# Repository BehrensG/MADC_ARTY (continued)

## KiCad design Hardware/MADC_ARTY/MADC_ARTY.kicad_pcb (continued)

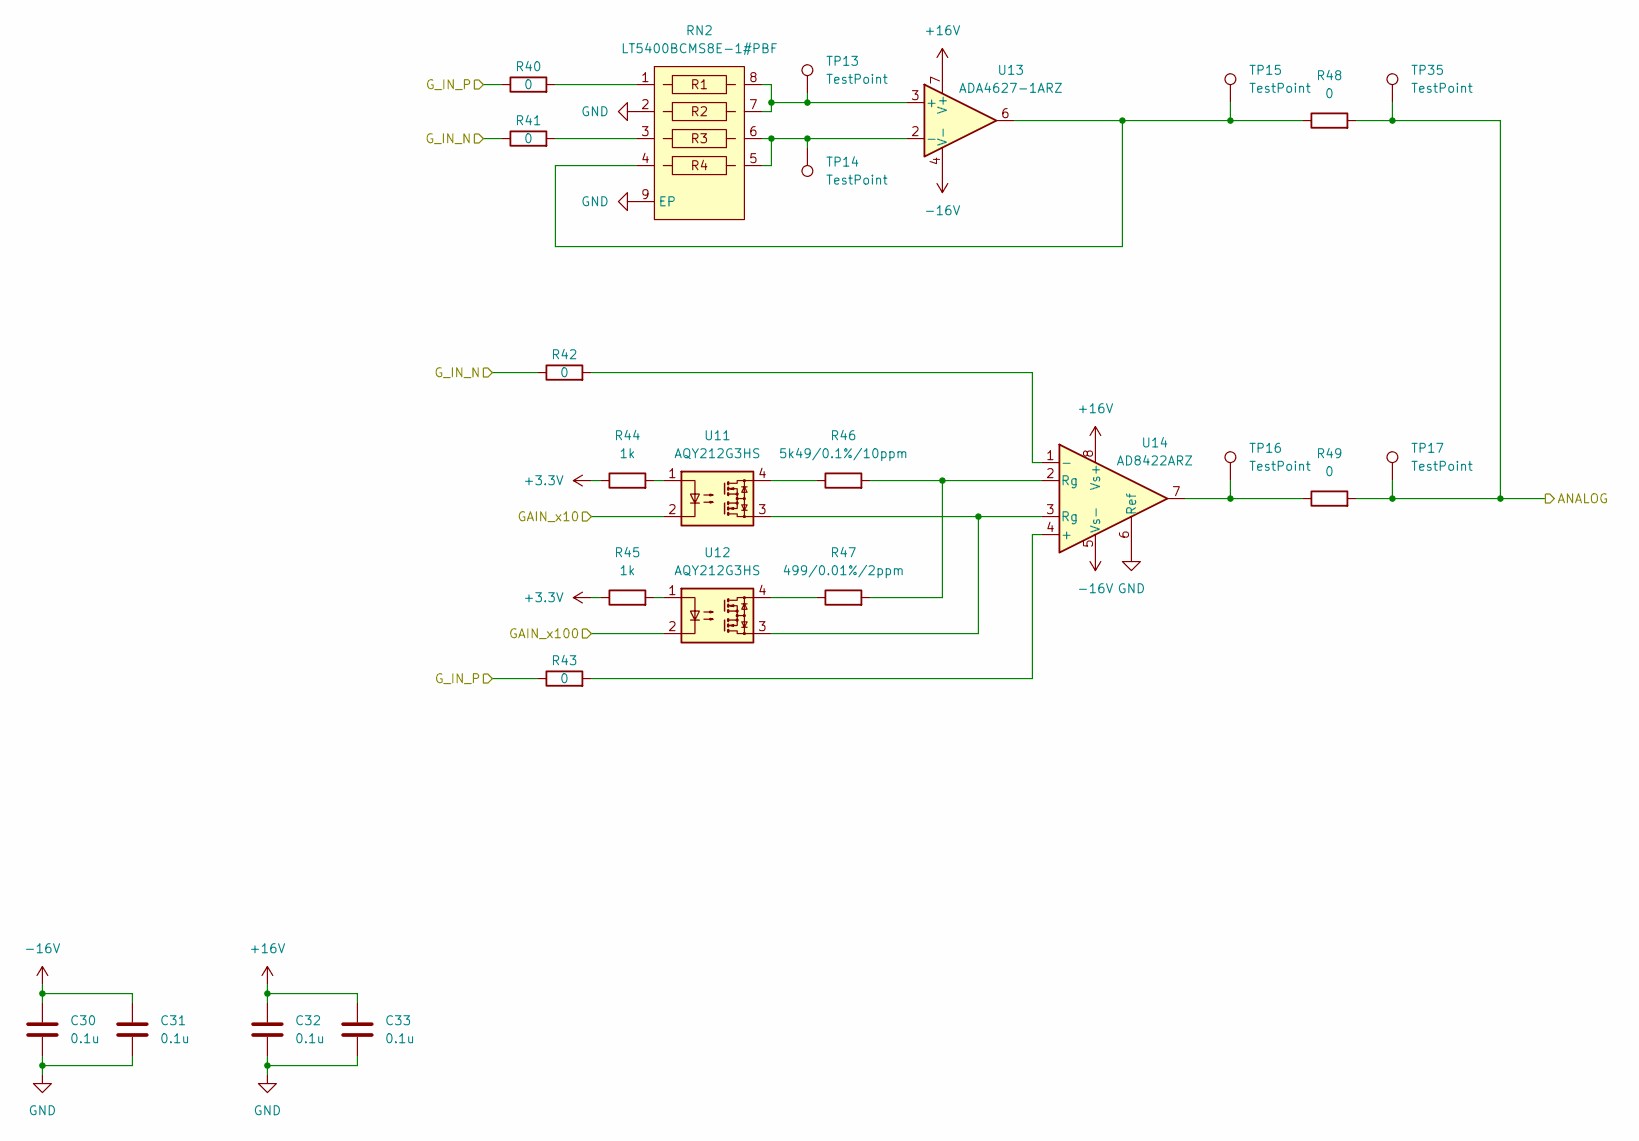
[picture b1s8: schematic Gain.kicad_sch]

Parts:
C30, C31, C32, C33: 0.1u; C_0603_1608Metric
R40, R41, R42, R43, R48, R49: 0; R_0603_1608Metric
R44, R45: 1k; R_0603_1608Metric
R46: 5k49/0.1%/10ppm; R_0603_1608Metric
R47: 499/0.01%/2ppm; R_0603_1608Metric
RN2: LT5400BCMS8E-1#PBF; MSOP-8-1EP_3x3mm_P0.65mm_EP1.73x1.85mm
TP13, TP14, TP15, TP16, TP17, TP35: TestPoint; TestPoint_Pad_D2.0mm
U11, U12: AQY212G3HS; SO-4_4.4x4.3mm_P2.54mm
U13: ADA4627-1ARZ; SOIC-8_3.9x4.9mm_P1.27mm
U14: AD8422ARZ; SOIC-8_3.9x4.9mm_P1.27mm

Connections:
+3.3V: R44.1, R45.1; also elsewhere on the board
+16V: C32.1, C33.1, U13.7 (V+), U14.8 (Vs+); also elsewhere on the board
-16V: C30.1, C31.1, U13.4 (V-), U14.5 (Vs-); also elsewhere on the board
/Block Diagram/ADC/AD_IN: R48.2, R49.2, TP17.1, TP35.1; also elsewhere on the board
/Block Diagram/Analog Channels1/OUT: R41.1, R42.1; also elsewhere on the board
/Block Diagram/Analog Channels/OUT: R40.1, R43.1; also elsewhere on the board
/Block Diagram/Gain/GAIN_x10: U11.2; also elsewhere on the board
/Block Diagram/Gain/GAIN_x100: U12.2; also elsewhere on the board
GND: C30.2, C31.2, C32.2, C33.2, RN2.2, RN2.9 (EP), U14.6 (Ref); also elsewhere on the board
unnamed: R40.2, RN2.1
unnamed: R41.2, RN2.3
unnamed: R44.2, U11.1
unnamed: R45.2, U12.1
unnamed: R46.1, U11.4
unnamed: R46.2, R47.2, U14.2 (Rg)
unnamed: R47.1, U12.4
unnamed: R48.1, RN2.4, TP15.1, U13.6
unnamed: R49.1, TP16.1, U14.7
unnamed: U11.3, U12.3, U14.3 (Rg)
unnamed: RN2.7, RN2.8, TP13.1, U13.3 (+)
unnamed: RN2.5, RN2.6, TP14.1, U13.2 (-)
unnamed: R43.2, U14.4 (+)
unnamed: R42.2, U14.1 (-)

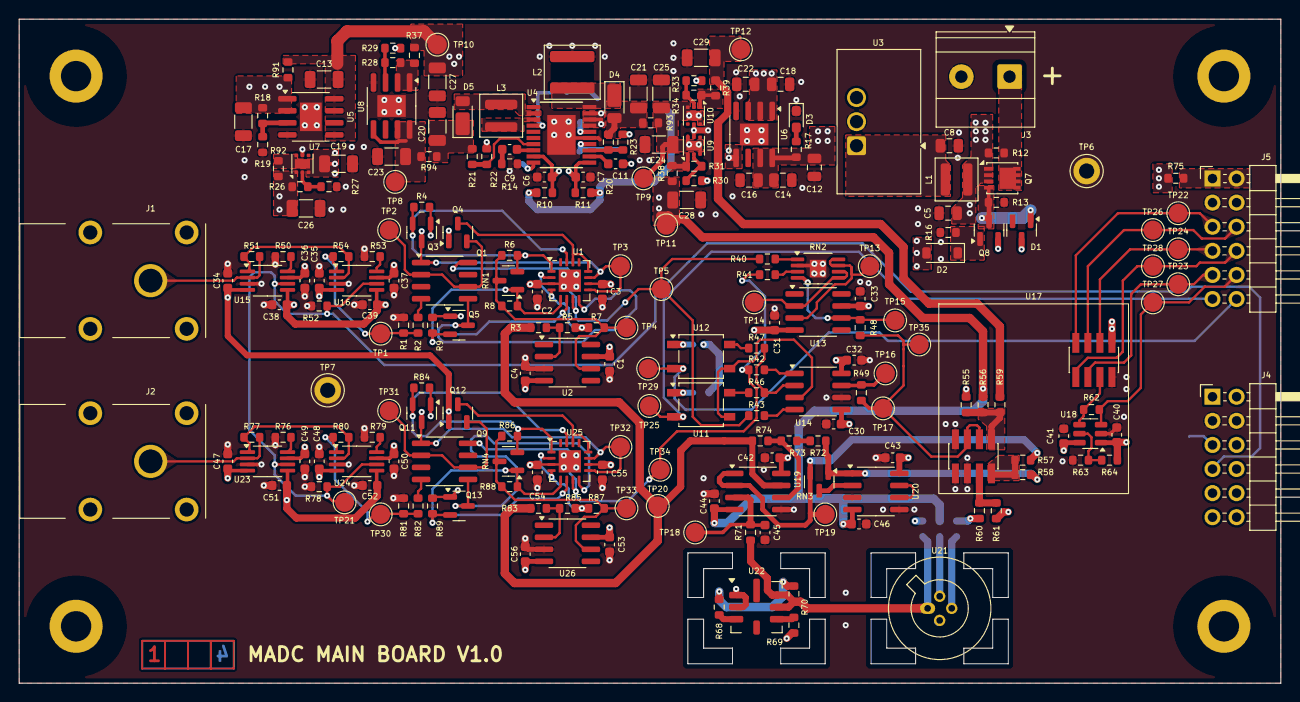
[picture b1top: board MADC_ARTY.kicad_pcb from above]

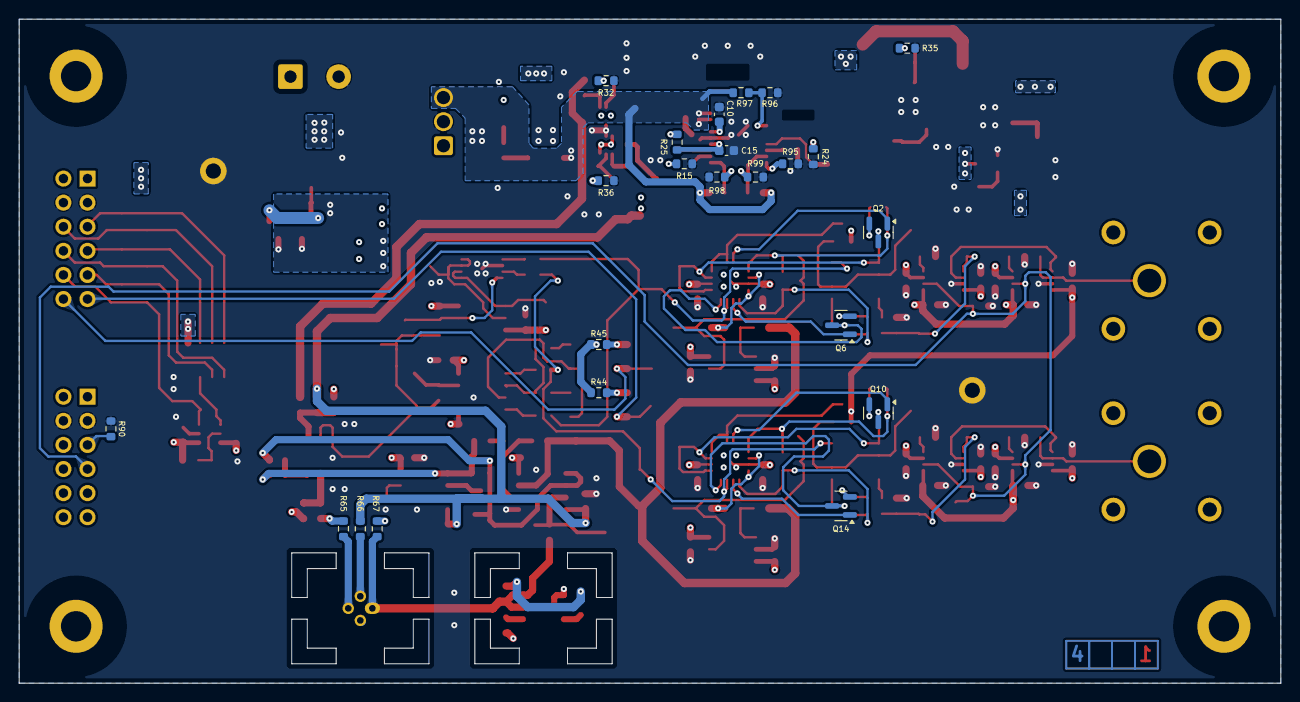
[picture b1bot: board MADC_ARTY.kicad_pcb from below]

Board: 4 copper layers, 133.0 x 70.0 mm, 251 parts (23 on the bottom side), 130 nets.

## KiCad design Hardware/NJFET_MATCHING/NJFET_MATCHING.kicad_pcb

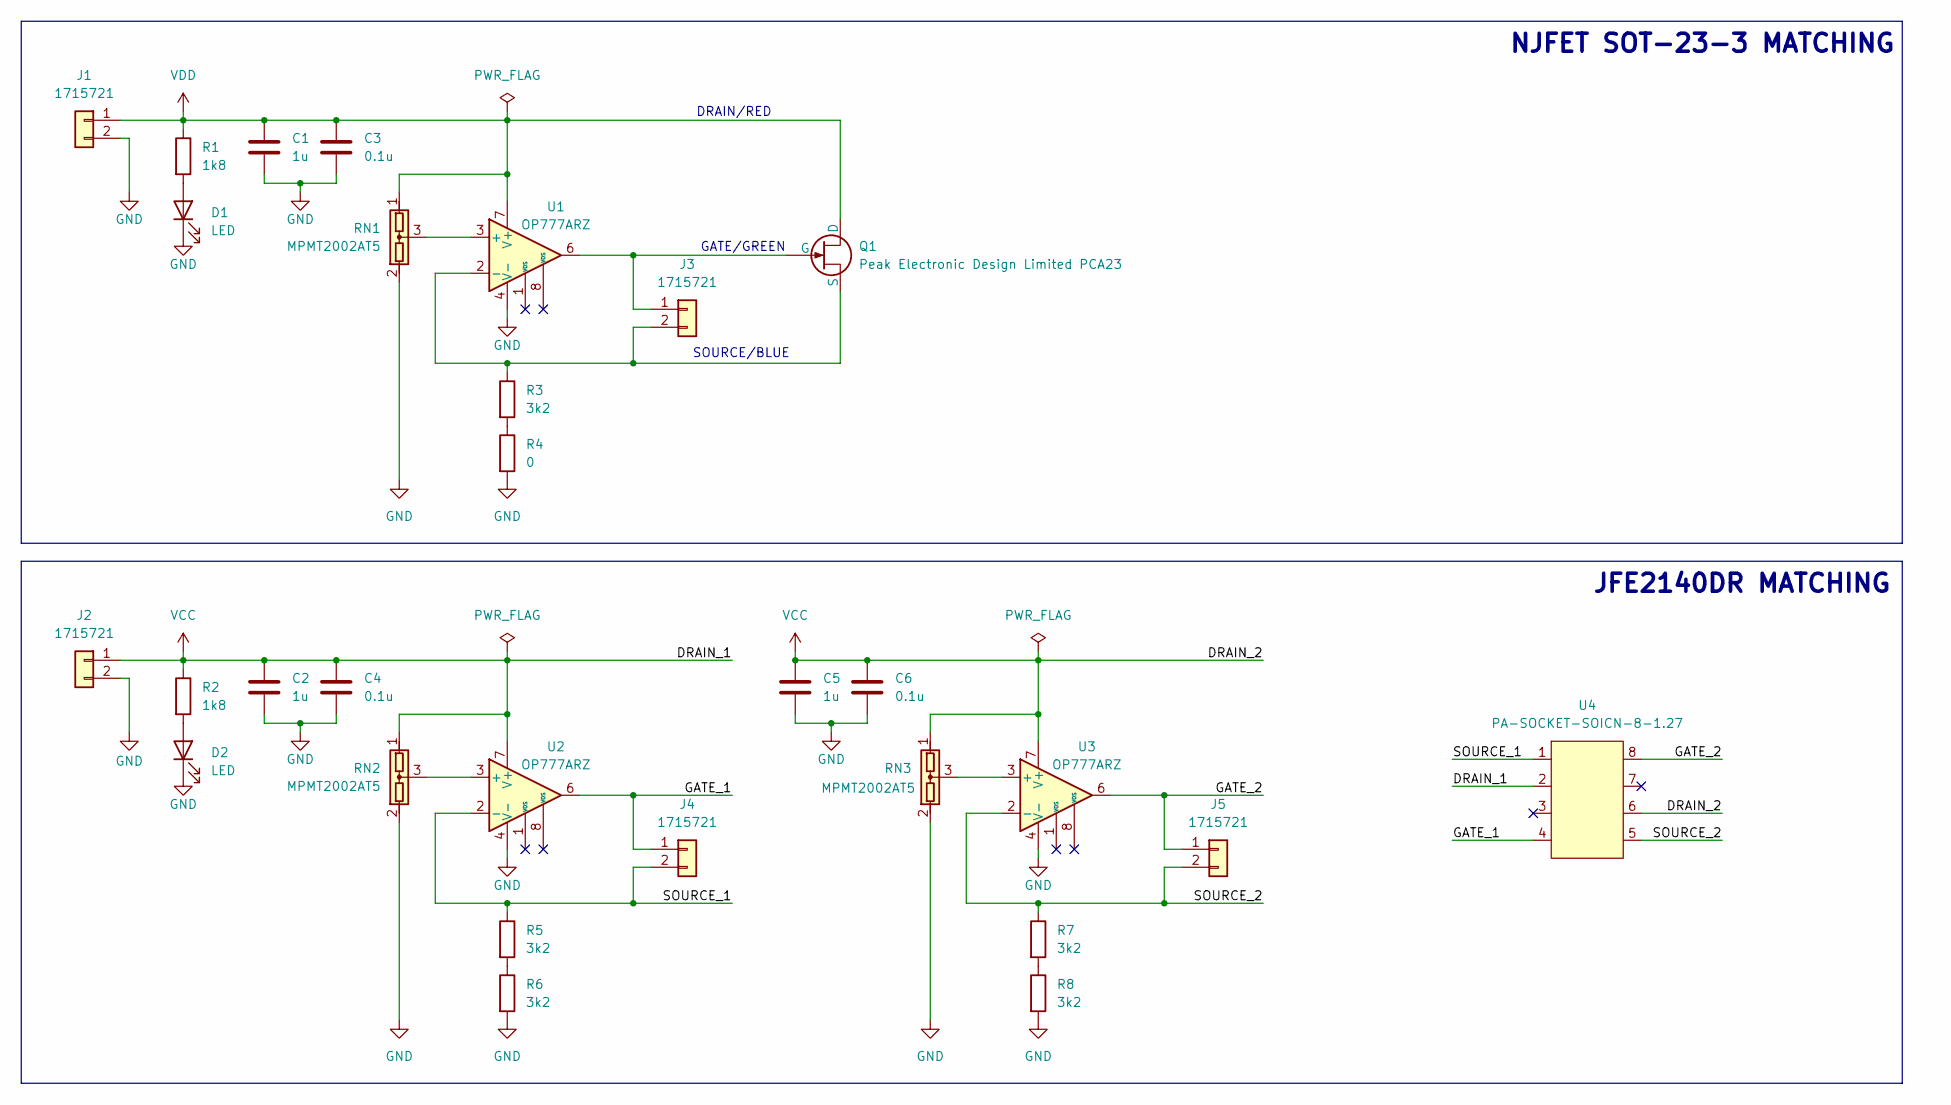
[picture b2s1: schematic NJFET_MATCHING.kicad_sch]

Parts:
C1, C2, C5: 1u; C_0603_1608Metric
C3, C4, C6: 0.1u; C_0603_1608Metric
D1, D2: LED; LED_0603_1608Metric
J1, J2, J3, J4, J5: 1715721; TerminalBlock_Phoenix_MKDS-1,5-2-5.08_1x02_P5.08mm_Horizont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
Q1: Peak Electronic Design Limited PCA23; PCA23
R1, R2: 1k8; R_0603_1608Metric
R3, R5, R6, R7, R8: 3k2; R_0603_1608Metric
R4: 0; R_0603_1608Metric
RN1, RN2, RN3: MPMT2002AT5; SOT-23
U1, U2, U3: OP777ARZ; SOIC-8_3.9x4.9mm_P1.27mm
U4: PA-SOCKET-SOICN-8-1.27; PA-SOCKET-SOICN-8-1_27

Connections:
/GATE_1: J4.1, U2.6, U4.4
/GATE_2: J5.1, U3.6, U4.8
/SOURCE_1: J4.2, R5.1, U2.2 (-), U4.1
/SOURCE_2: J5.2, R7.1, U3.2 (-), U4.5
GND: C1.2, C2.2, C3.2, C4.2, C5.2, C6.2, D1.1 (K), D2.1 (K), J1.2, J2.2, R4.2, R6.2, R8.2, RN1.2, RN2.2, RN3.2, U1.4 (V-), U2.4 (V-), U3.4 (V-)
unnamed: D1.2 (A), R1.2
unnamed: D2.2 (A), R2.2
unnamed: J3.1, Q1.2 (G), U1.6
unnamed: J3.2, Q1.3 (S), R3.1, U1.2 (-)
unnamed: R3.2, R4.1
unnamed: R5.2, R6.1
unnamed: R7.2, R8.1
unnamed: RN1.3, U1.3 (+)
unnamed: RN2.3, U2.3 (+)
unnamed: RN3.3, U3.3 (+)
VCC: C2.1, C4.1, C5.1, C6.1, J2.1, R2.1, RN2.1, RN3.1, U2.7 (V+), U3.7 (V+), U4.2, U4.6
VDD: C1.1, C3.1, J1.1, Q1.1 (D), R1.1, RN1.1, U1.7 (V+)

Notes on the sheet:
JFE2140DR MATCHING
NJFET SOT-23-3 MATCHING
SOURCE/BLUE
GATE/GREEN
DRAIN/RED

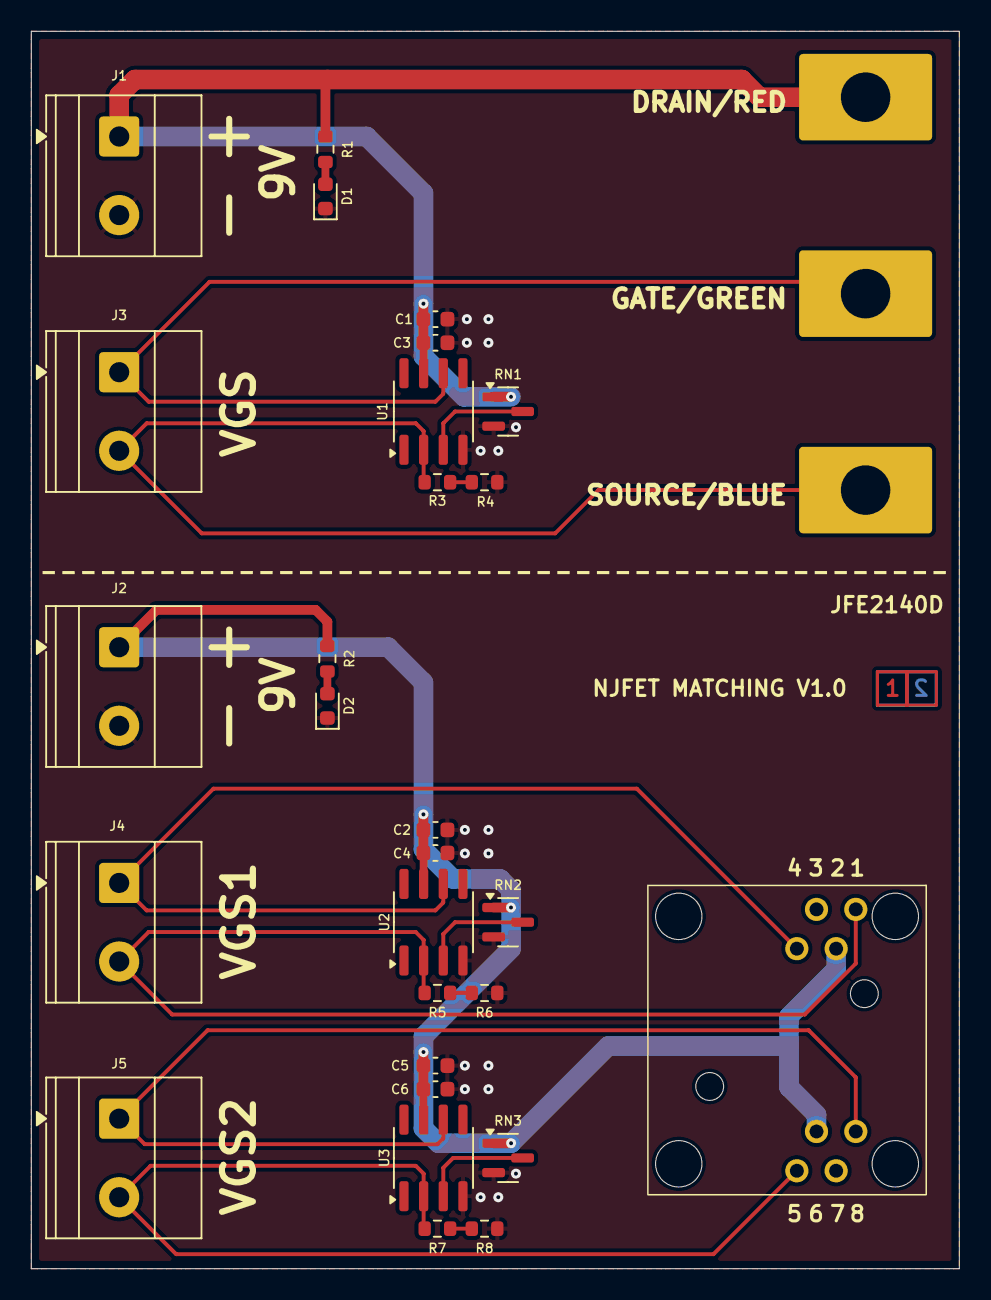
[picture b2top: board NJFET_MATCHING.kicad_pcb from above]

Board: 2 copper layers, 60.0 x 80.0 mm, 29 parts (0 on the bottom side), 17 nets.

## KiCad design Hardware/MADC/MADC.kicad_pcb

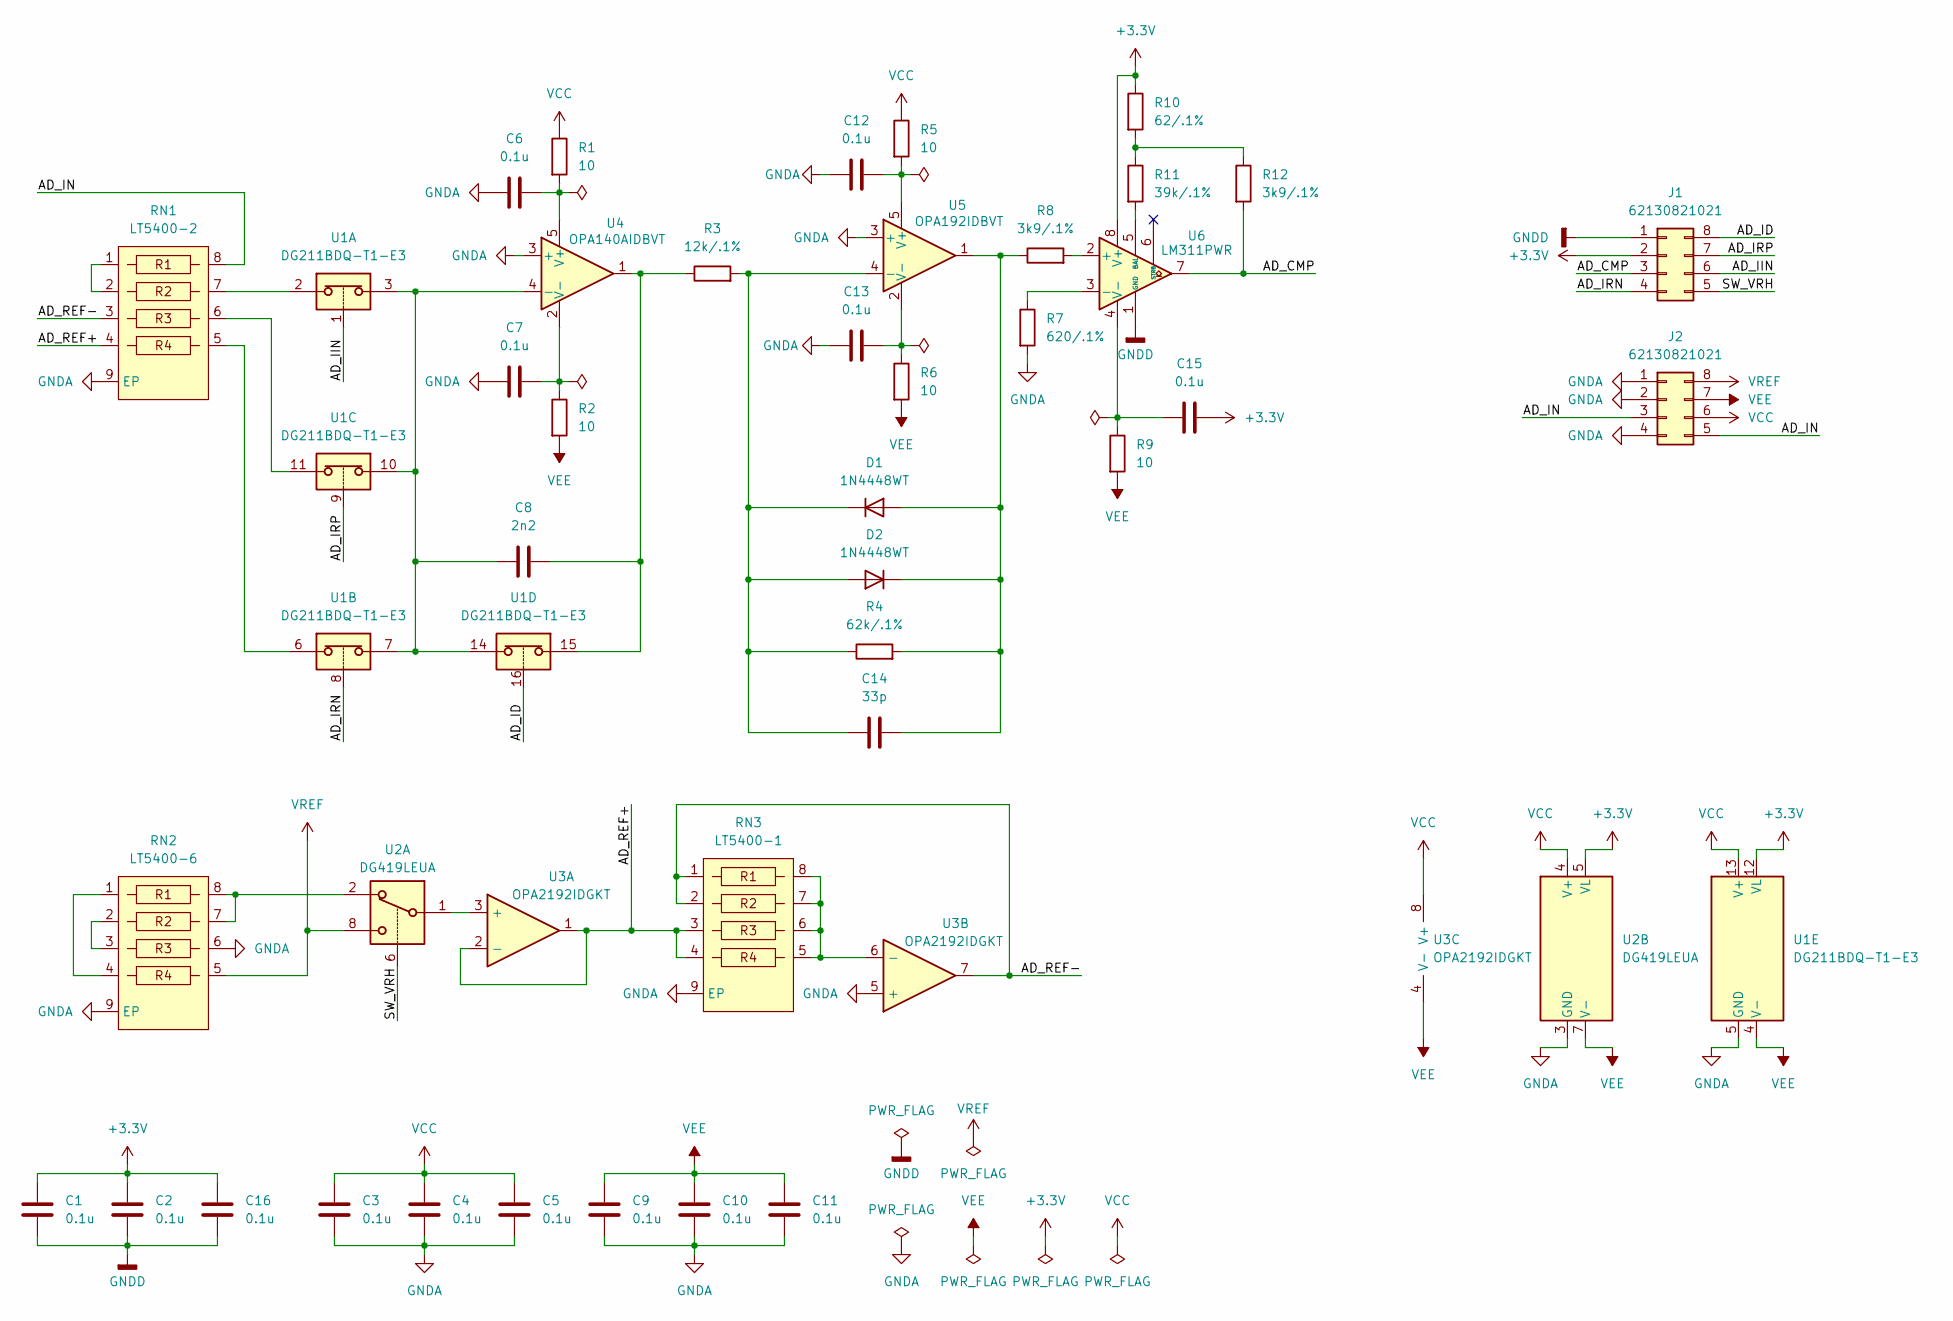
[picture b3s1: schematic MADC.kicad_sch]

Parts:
C1, C2, C3, C4, C5, C6, C7, C9, C10, C11, C12, C13, C15, C16: 0.1u; C_0402_1005Metric_Pad0.74x0.62mm_HandSolder
C8: 2n2; C_0603_1608Metric
C14: 33p; C_0402_1005Metric_Pad0.74x0.62mm_HandSolder
D1, D2: 1N4448WT; D_SOD-323
J1, J2: 62130821021; PinHeader_2x04_P1.27mm_Vertical_SMD
R1, R2, R5, R6, R9: 10; R_0402_1005Metric_Pad0.72x0.64mm_HandSolder
R3: 12k/.1%; R_0402_1005Metric_Pad0.72x0.64mm_HandSolder
R4: 62k/.1%; R_0402_1005Metric_Pad0.72x0.64mm_HandSolder
R7: 620/.1%; R_0402_1005Metric_Pad0.72x0.64mm_HandSolder
R8, R12: 3k9/.1%; R_0402_1005Metric_Pad0.72x0.64mm_HandSolder
R10: 62/.1%; R_0402_1005Metric_Pad0.72x0.64mm_HandSolder
R11: 39k/.1%; R_0402_1005Metric_Pad0.72x0.64mm_HandSolder
RN1: LT5400-2; MSOP-8-1EP_3x3mm_P0.65mm_EP1.73x1.85mm
RN2: LT5400-6; MSOP-8-1EP_3x3mm_P0.65mm_EP1.73x1.85mm
RN3: LT5400-1; MSOP-8-1EP_3x3mm_P0.65mm_EP1.73x1.85mm
U1: DG211BDQ-T1-E3; TSSOP-16_4.4x5mm_P0.65mm
U2: DG419LEUA; MSOP-8_3x3mm_P0.65mm
U3: OPA2192IDGKT; VSSOP-8_3x3mm_P0.65mm
U4: OPA140AIDBVT; SOT-23-5
U5: OPA192IDBVT; SOT-23-5
U6: LM311PWR; TSSOP-8_4.4x3mm_P0.65mm

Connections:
+3.3V: C1.2, C2.2, C15.2, C16.2, J1.2, R10.1, U1.12 (VL), U2.5 (VL), U6.8 (V+)
/AD_CMP: J1.3, R12.2, U6.7
/AD_ID: J1.8, U1.16
/AD_IIN: J1.6, U1.1
/AD_IN: J2.3, J2.5, RN1.8
/AD_IRN: J1.4, U1.8
/AD_IRP: J1.7, U1.9
/AD_REF+: RN1.4, RN3.3, RN3.4, U3.1, U3.2 (-)
/AD_REF-: RN1.3, RN3.1, RN3.2, U3.7
/SW_VRH: J1.5, U2.6
GNDA: C3.1, C4.1, C5.1, C6.1, C7.1, C9.1, C10.1, C11.1, C12.1, C13.1, J2.1, J2.2, J2.4, R7.2, RN1.9 (EP), RN2.6, RN2.9 (EP), RN3.9 (EP), U1.5 (GND), U2.3 (GND), U3.5 (+), U4.3 (+), U5.3 (+)
GNDD: C1.1, C2.1, C16.1, J1.1, U6.1 (GND)
unnamed: C8.2, R3.1, U1.15, U4.1
unnamed: C14.2, D1.2 (A), D2.1 (K), R4.2, R8.1, U5.1
unnamed: C14.1, D1.1 (K), D2.2 (A), R3.2, R4.1, U5.4 (-)
unnamed: R10.2, R11.1, R12.1
unnamed: RN1.1, RN1.2
unnamed: RN1.5, U1.6
unnamed: RN1.6, U1.11
unnamed: RN1.7, U1.2
unnamed: RN2.1, RN2.4
unnamed: RN2.2, RN2.3
unnamed: RN2.7, RN2.8, U2.2
unnamed: U2.1, U3.3 (+)
unnamed: RN3.5, RN3.6, RN3.7, RN3.8, U3.6 (-)
unnamed: C8.1, U1.3, U1.7, U1.10, U1.14, U4.4 (-)
unnamed: C6.2, R1.2, U4.5 (V+)
unnamed: C7.2, R2.1, U4.2 (V-)
unnamed: C12.2, R5.2, U5.5 (V+)
unnamed: C13.2, R6.1, U5.2 (V-)
unnamed: R8.2, U6.2 (+)
unnamed: R7.1, U6.3 (-)
unnamed: R11.2, U6.5 (BAL)
unnamed: C15.1, R9.1, U6.4 (V-)
VCC: C3.2, C4.2, C5.2, J2.6, R1.1, R5.1, U1.13 (V+), U2.4 (V+), U3.8 (V+)
VEE: C9.2, C10.2, C11.2, J2.7, R2.2, R6.2, R9.2, U1.4 (V-), U2.7 (V-), U3.4 (V-)
VREF: J2.8, RN2.5, U2.8

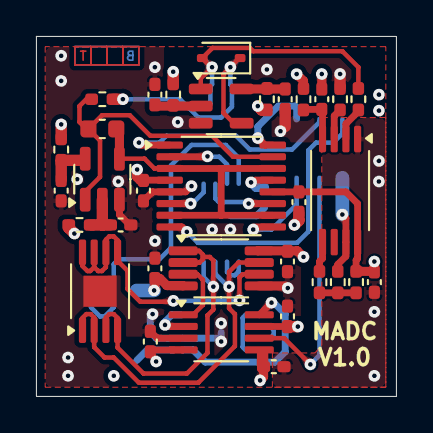
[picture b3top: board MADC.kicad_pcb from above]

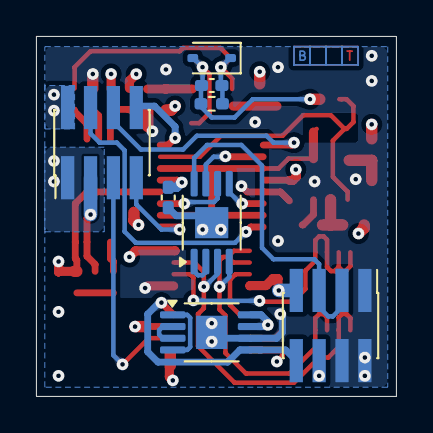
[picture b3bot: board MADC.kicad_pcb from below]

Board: 4 copper layers, 20.0 x 20.0 mm, 41 parts (8 on the bottom side), 37 nets.

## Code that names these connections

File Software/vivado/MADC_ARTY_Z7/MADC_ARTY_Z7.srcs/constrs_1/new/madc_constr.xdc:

set_property IOSTANDARD LVCMOS33 [get_ports {ctr_4bits_tri_o[3]}]
set_property IOSTANDARD LVCMOS33 [get_ports {ctr_4bits_tri_o[2]}]
set_property IOSTANDARD LVCMOS33 [get_ports {ctr_4bits_tri_o[1]}]
set_property IOSTANDARD LVCMOS33 [get_ports {ctr_4bits_tri_o[0]}]
set_property OFFCHIP_TERM NONE [get_ports ad_id]
set_property OFFCHIP_TERM NONE [get_ports ad_iin]
set_property OFFCHIP_TERM NONE [get_ports ad_irn]
set_property OFFCHIP_TERM NONE [get_ports ad_irp]
set_property OFFCHIP_TERM NONE [get_ports sw_vrh]
set_property PACKAGE_PIN V18 [get_ports {ctr_4bits_tri_o[0]}]
set_property PACKAGE_PIN T14 [get_ports {ctr_4bits_tri_o[1]}]
set_property PACKAGE_PIN U12 [get_ports {ctr_4bits_tri_o[2]}]
set_property PACKAGE_PIN T16 [get_ports {ctr_4bits_tri_o[3]}]
set_property IOSTANDARD LVCMOS33 [get_ports ad_cmp]
set_property IOSTANDARD LVCMOS33 [get_ports ad_id]
set_property IOSTANDARD LVCMOS33 [get_ports ad_iin]
set_property IOSTANDARD LVCMOS33 [get_ports ad_irn]
set_property IOSTANDARD LVCMOS33 [get_ports ad_irp]
set_property IOSTANDARD LVCMOS33 [get_ports sw_vrh]
set_property PACKAGE_PIN V13 [get_ports sw_vrh]
set_property PACKAGE_PIN V15 [get_ports ad_cmp]
set_property PACKAGE_PIN U17 [get_ports ad_id]
set_property PACKAGE_PIN V17 [get_ports ad_iin]
set_property PACKAGE_PIN T15 [get_ports ad_irn]
set_property PACKAGE_PIN R16 [get_ports ad_irp]

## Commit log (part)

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2025-08-14 Copy
2025-08-14 GERBER
2025-08-24 Analog part works, made CMRR measurements
